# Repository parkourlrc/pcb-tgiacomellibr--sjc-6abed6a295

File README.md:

# Single Joint Control Board (SJC)

- 3 Encoder inputs
- 2 Isolated inputs
- 2 Endstop inputs
- 2 Digital outputs
- Servomotor interface with current sense and pwm output

## Communication library:  

1. Install packages and deps.:
    ```
    sudo apt update
    sudo apt install build-essential git g++ cmake manpages-dev nlohmann-json3-dev
    sudo apt install libmodbus-dev
    ```

2. Acquire SJC packages:
    ``` 
    git clone https://github.com/tgiacomellibr/sjc.git
    ```

3. Create build directory:
    ```
    cd sjc/software
    mkdir -p build && cd build
    ```

4. Configure, compile and install system-wide (default prefix `/usr/local`):
    ```
    cmake ..
    make
    sudo make install
    sudo ldconfig
    ```

    > To install in a custom location instead, pass `-DCMAKE_INSTALL_PREFIX=/path/to/install` to `cmake` (e.g. `$HOME/.local`). In that case `sudo` is not required and you may need to extend `LD_LIBRARY_PATH` / `CMAKE_PREFIX_PATH` to find the library.

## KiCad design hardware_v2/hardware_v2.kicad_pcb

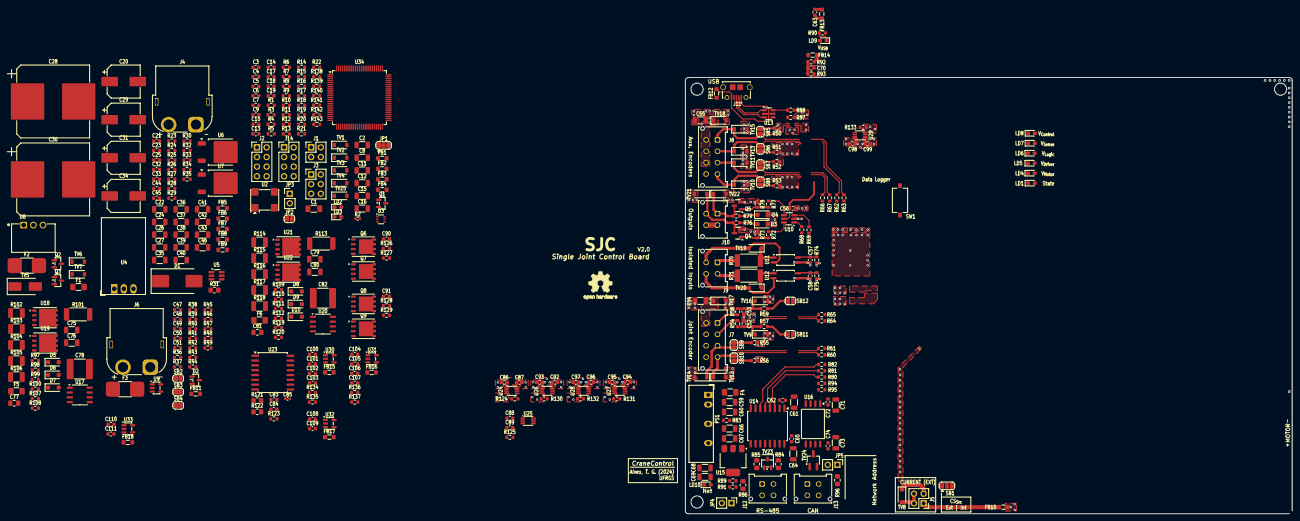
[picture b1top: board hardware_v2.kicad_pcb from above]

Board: 4 copper layers, 160.0 x 115.0 mm, 403 parts (0 on the bottom side), 212 nets.

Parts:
C1: 4.7uF 10% 50V; C_1206_3216Metric_Pad1.33x1.80mm_HandSolder
C2, C8, C11, C12, C38, C39, C54, C55, C67, C68, C76, C80: 1uF 10% 50V; C_1206_3216Metric
C3, C5, C6, C7, C9, C10, C13, C14, C17, C18, C19, C25, C32, C33, C44, C45, C48, C49, C50, C56, C62, C63, C65, C72, C74, C83, C86, C87, C88, C89, C92, C93, C94, C95, C96, C97, C98, C99, C100, C101, C102, C104, C105, C106, C108, C110: 100nF 5% 50V; C_0603_1608Metric
C4, C21, C23, C51, C57, C58, C70, C84, C90, C91, C103, C107, C109, C111: 10nF 5% 50V; C_0603_1608Metric
C15, C16: 2.2uF 10% 50V; C_1206_3216Metric
C20, C34: 47uF 63V 20%; CP_Elec_8x10.5
C22, C24, C26, C27, C35, C36, C40, C41, C42, C46, C60, C61, C64, C66, C69, C71, C73, C75, C79: 10uF 10% 50V; C_1206_3216Metric
C28, C30: 680uF 63V 20%; CP_Elec_18x17.5
C29, C31: 100uF 63V 20%; CP_Elec_8x10.5
C37, C43, C59: 22uF 10% 25V; C_1206_3216Metric
C47: 1.5nF 5% 50V; C_0603_1608Metric
C52, C53: 22nF 5% 50V; C_0603_1608Metric
C77, C81: 100nF 5% 50V; C_0805_2012Metric_Pad1.18x1.45mm_HandSolder
C78, C82: 22uF 20% 50V; C_2220_5750Metric
C85: 220pF 5% 50V; C_0402_1005Metric_Pad0.74x0.62mm_HandSolder
D1: B560C; D_SMC_Handsoldering
D2: BAT54S; SOT-23
D3, D4, D5, D6, D7, D8, D9, D10: PMEG60T30ELR; D_SOD-123F
F1, F5, F6: 30V 1100mA; Fuse_1206_3216Metric_Pad1.42x1.75mm_HandSolder
F2, F3: 40A 63V; Fuse_2410_6125Metric_CB61F
F4: 13.2V 500mA; Fuse_1206_3216Metric_Pad1.42x1.75mm_HandSolder
FB1, FB2, FB3, FB4, FB5, FB6, FB7, FB8, FB9, FB10, FB11, FB12, FB13, FB14, FB15, FB16, FB17, FB18: 220R 3A; L_0805_2012Metric_Pad1.05x1.20mm_HandSolder
H1, H2, H3, H4: MountingHole; MountingHole_3.2mm_M3_ISO7380
J1: Aux Usart; PinHeader_2x02_P2.54mm_Vertical
J2: PROG_{DBG}; PinHeader_2x04_P2.54mm_Vertical
J3: NET ADDRESS; PinHeader_2x03_P2.54mm_Vertical
J4: V_{POWER}; AMASS_XT60PW-F_1x02_P7.20mm_Horizontal
J5: EXT-CS; PinHeader_2x02_P2.54mm_Vertical
J6: Motor; AMASS_XT60PW-F_1x02_P7.20mm_Horizontal
J7: Joint encoders; Molex_Micro-Fit_3.0_43045-0812_2x04_P3.00mm_Vertical
J8: Aux. encoders; Molex_Micro-Fit_3.0_43045-0812_2x04_P3.00mm_Vertical
J9: Isolated Inputs; Molex_Micro-Fit_3.0_43045-0412_2x02_P3.00mm_Vertical
J10: Outputs; Molex_Micro-Fit_3.0_43045-0412_2x02_P3.00mm_Vertical
J11: AMPHENOL_10118194-0001LF
J12, J13: RS-485; Molex_Micro-Fit_3.0_43045-0412_2x02_P3.00mm_Vertical
J14: SPI; PinHeader_2x04_P2.54mm_Vertical
JP1: CS_AD_SEL; SolderJumper-3_P1.3mm_Bridged12_RoundedPad1.0x1.5mm
JP2: CS_AD_SEL; SolderJumper-2_P1.3mm_Open_RoundedPad1.0x1.5mm
JP3: Boot; PinHeader_1x02_P2.54mm_Vertical
JP4, JP5: RS-485 TERM; PinHeader_1x02_P2.54mm_Vertical
LD1, LD2, LD3, LD4, LD5, LD6, LD7, LD8, LD9, LD10: 1.8V @ 5mA; LED_0603_1608Metric_Pad1.05x0.95mm_HandSolder
PS1: IB0512LS-1WR3; IB_LS-1WR3
Q1: BC817; SOT-23
Q2, Q3, Q4, Q5: NDS7002A; SOT-23
Q6, Q7, Q8, Q9: SI7149ADP; PowerPAK_SO-8_Single
R1, R27, R28, R49, R57, R59, R72, R77, R98, R110: 1k 1%; R_0603_1608Metric
R2: 47R 1%; R_0402_1005Metric_Pad0.72x0.64mm_HandSolder
R3, R14, R15, R16, R17, R23, R26, R36, R43, R89, R123: 10k 1%; R_0603_1608Metric
R4, R21, R22, R35: 330R 1%; R_0603_1608Metric
R5, R6, R8, R9, R10, R11, R12, R13, R18, R19, R20, R44, R45, R46, R47, R60, R61, R62, R63, R64, R65, R66, R67, R68, R69, R80, R81, R82, R94, R95, R97, R109, R138, R139, R140, R141, R142, R143: 33R 1%; R_0603_1608Metric
R7, R24, R25, R29, R30, R41, R73, R78, R83, R99, R100, R107, R108, R111, R112, R119, R120, R124, R125, R127, R129, R130, R131, R132, R133: 100k 1%; R_0603_1608Metric
R31: 5.62k 5% 250mW; R_0805_2012Metric_Pad1.20x1.40mm_HandSolder
R32, R33, R74, R75, R76, R79: 2k 5%; R_0603_1608Metric
R34, R90, R91: 680R 1%; R_0603_1608Metric
R37, R38: 1.1k 0.1%; R_0603_1608Metric
R39: 560R 0.1%; R_0603_1608Metric
R40, R42, R48, R134, R135, R136, R137: 1.58k 0.1%; R_0603_1608Metric
R50, R51, R52, R53, R55, R56: 2k7 1%; R_0603_1608Metric
R54, R58: 1.5k 1%; R_0603_1608Metric
R70, R71: 1.6k 5% 1W; R_2512_6332Metric_Pad1.40x3.35mm_HandSolder
R84, R85: 10R 5% 1/2W; R_0805_2012Metric_Pad1.20x1.40mm_HandSolder
R86, R96: 120R 0.1% 1/8W; R_0805_2012Metric_Pad1.20x1.40mm_HandSolder
R87, R88: 22R 1%; R_0603_1608Metric
R92: 33k 0.1%; R_0603_1608Metric
R93, R126, R128: 82k 0.1%; R_0603_1608Metric
R101, R113: 2R 5% 2W; R_2512_6332Metric_Pad1.40x3.35mm_HandSolder
R102, R105, R114, R117: 10R 1% 500mW; R_1210_3225Metric_Pad1.30x2.65mm_HandSolder
R103, R106, R115, R118: 62R 1% 500mW; R_1210_3225Metric_Pad1.30x2.65mm_HandSolder
R104, R116: 0R 1% 500mW; R_1210_3225Metric_Pad1.30x2.65mm_HandSolder
R121: 8k2 1% 1/8W; R_0805_2012Metric_Pad1.20x1.40mm_HandSolder
R122: 1k5 1% 1/8W; R_0805_2012Metric_Pad1.20x1.40mm_HandSolder
SB1: CS_SEL; SolderJumper-3_P1.3mm_Open_RoundedPad1.0x1.5mm
SB2, SB5, SB6, SB7, SB8, SB9, SB10, SB11, SB12: SolderJumper-2_P1.3mm_Open_RoundedPad1.0x1.5mm
SB3, SB4: SolderJumper-2_P1.3mm_Bridged2Bar_RoundedPad1.0x1.5mm
SW1: Tactile Switch; SW_Tactile_SPST_NO_Straight_CK_PTS636Sx25SMTRLFS
SYM1: Logo_Open_Hardware_Small; OSHW-Logo2_9.8x8mm_SilkScreen
TV1, TV2, TV3, TV4, TV7, TV25: PTVS3V3S1UR; D_SOD-123
TV5: SMBJ30A; D_SMB_Handsoldering
TV6, TV8, TV9, TV10, TV11, TV13, TV15, TV16, TV18: PTVS5V0S1UR; D_SOD-123
TV12, TV14, TV17, TV21, TV22: PTVS12VS1UR; D_SOD-123
TV19, TV20: PTVS30VS1UR; D_SOD-123
TV23: SM712; SOT-23-3
TV24: PESD2CANFD24L; SOT-23W_Handsoldering
U2: YSO110TR-16MHz; Oscillator_SMD_YXC_YSO110TR_7050-4Pin_7.0x5.0mm
U3: 74LVC2G17GW; SOT-363_SC-70-6
U4: R-78K12-2.0L; Converter_DCDC_RECOM_R-78K-2.0L_THT
U5, U10: SN74LVC2G04; SOT-23-6_Handsoldering
U6: NCP1117DT50; TO-252-2
U7: NCP1117DT33; TO-252-2
U8: VXO78012-1000; CONV_VXO78012-1000
U9, U30, U31, U32, U33: TLV9051; SOT-23-5
U11, U12: TLP291; SOP-4_4.4x2.6mm_P1.27mm
U13: USBLC6-4SC6; SOT-23-6
U14: ISO1430B; SOIC-16W_7.5x10.3mm_P1.27mm
U15: LD1117S50TR; SOT-223-3_TabPin2
U16: ISO1042; SOIC-8_7.5x5.85mm_P1.27mm
U17, U20: 2ED2184S06F; Infineon_PG-DSO-8-24_4x5mm
U18, U19, U21, U22: IAUC100N04S6N028; Infineon_PG-TDSON-8_6.15x5.15mm
U23: ACS733KLATR-40AB; SOIC-16W_7.5x10.3mm_P1.27mm
U24, U25, U26, U27, U28, U29: 74LVC2T45DC; VSSOP-8_2.3x2mm_P0.5mm
U34: STM32H750VBTx; LQFP-100_14x14mm_P0.5mm

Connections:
+3V3: C1.2, C2.2, C3.2, C5.2, C7.2, C9.2, C10.2, C11.2, C13.2, C19.1, C25.1, C42.2, C45.2, C56.1, C61.2, C62.1, C71.2, C72.1, C86.2, C88.2, C93.1, C95.1, C97.1, C99.1, D2.2, FB1.1, FB3.2, FB11.2, FB15.2, FB16.2, FB17.2, FB18.2, J1.3, J2.2, J3.1, J3.3, J3.5, J14.5, JP3.1, LD1.2 (A), LD8.2 (A), R24.2, R25.2, R74.2, R75.2, R124.2, R125.2, TV1.1 (K), TV2.1 (K), TV7.1 (K), TV25.1 (K), U3.5 (VCC), U5.5 (V_{CC}), U7.2 (VO), U10.5 (V_{CC}), U14.1 (VCC1), U16.1 (VCC1), U24.1 (VCCA), U25.1 (VCCA), U26.1 (VCCA), U27.1 (VCCA), U28.1 (VCCA), U29.1 (VCCA), U34.6 (VBAT), U34.11 (VDD), U34.27 (VDD), U34.50 (VDD), U34.75 (VDD), U34.100 (VDD)
+3V3A: C4.2, C6.2, C8.2, FB1.2, R2.2, U34.21 (VDDA)
+3V3_OSC: C18.1, FB3.1, R17.2, U2.4 (V_{DD})
+3V3_SENSE: C83.1, C84.1, R121.1, R123.2, U23.15 (VCC), U23.16 (VCC)
+5V: C41.2, C44.2, C54.2, C55.2, C87.1, C89.1, C92.2, C94.2, C96.2, C98.2, D3.2 (A), D4.2 (A), F4.2, FB10.1, J7.5, J7.7, J8.5, J8.7, LD7.2 (A), R50.1, R51.1, R52.1, R53.1, R55.2, R56.2, TV6.1 (K), TV17.1 (K), TV18.1 (K), U6.2 (VO), U24.8 (VCCB), U25.8 (VCCB), U26.8 (VCCB), U27.8 (VCCB), U28.8 (VCCB), U29.8 (VCCB)
+5V_ISO: C64.1, C65.1, C68.2, C69.2, C73.1, C74.1, R89.2, R91.1, U14.16 (VCC2), U15.2 (VO), U16.8 (VCC2)
+5V_USB: FB14.2, J11.1 (VBUS), LD9.2 (A), U13.5 (VBUS)
+12V: C32.2, C33.2, C43.2, C46.2, FB6.2, FB8.1, LD6.2 (A), U8.3 (+V_{OUT})
/Communication/485_XCVR_DE: R81.1, U14.4 (~RE), U14.5 (DE)
/Communication/485_XCVR_DI: R82.1, U14.6 (D)
/Communication/485_XCVR_RO: R80.2, U14.3 (R)
/Communication/+12V_ISO_DC: C66.2, C67.2, PS1.6 (+Vout), R83.2, U15.3 (VI)
/Communication/CAN_XCVR_RX: R94.2, U16.3 (RXD)
/Communication/CAN_XCVR_TX: R95.1, U16.2 (TXD)
/Communication/CAN_{H}: J13.2, R96.1, TV24.2 (K2), U16.7 (CANH)
/Communication/CAN_{L}: J13.1, JP5.2, TV24.1 (K1), U16.6 (CANL)
/Communication/COM_USB_V_{BUS}_SIG: C70.2, R92.2, R93.2
/Communication/RS_485_{A}: J12.1, R85.1, R86.1, TV23.1
/Communication/RS_485_{B}: J12.2, JP4.1, R84.1, TV23.2
/Communication/RS_{A}: R85.2, U14.12 (A)
/Communication/RS_{B}: R84.2, U14.13 (B)
/Communication/USB_D+: J11.3 (D+), R87.2, U13.3 (I/O2), U13.4 (I/O3)
/Communication/USB_D-: J11.2 (D-), R88.2, U13.1 (I/O1), U13.6 (I/O4)
/Control/BOOT: JP3.2, R7.2
/Control/CURRENT_SIGNAL_FILT: JP1.2 (C), R40.2, SB4.2 (B)
/Control/DBG_USART_TX: J2.5, R12.2
/Control/GP_ISO_IN_A: C57.2, R74.1, U11.4
/Control/GP_ISO_IN_B: C58.2, R75.1, U12.4
/Control/JTCK/SWCLK: J2.7, R11.2
/Control/JTDI: J2.6, R9.2
/Control/JTDO/TRACESWO: J2.4, R8.2
/Control/JTMS/SWDIO: J2.8, R10.2
/Control/MOTOR_INPUT_VOLTAGE_SIG: R49.2, U33.1, U33.4 (-)
/Control/MotorDriver_{EN}: C21.2, R24.1, U5.1 (1A)
/Control/MotorPSU_{EN}: C23.2, R25.1, U5.3 (2A)
/Control/NET_ADDR_A: J3.2, R14.1
/Control/NET_ADDR_B: J3.4, R15.1
/Control/NET_ADDR_C: J3.6, R16.1
/Control/NJTRST: J2.3, R13.2
/Control/NRST: C17.2, SW1.2
/Control/R_MOT_HI_{PWM}: JP2.1 (A), R46.2
/Control/SPI_CSEL_{PIN}: J14.6, R142.1
/Control/SPI_INT_{PIN}: J14.8, R143.1
/Control/SPI_MISO_{PIN}: J14.2, R140.1
/Control/SPI_MOSI_{PIN}: J14.1, R139.1
/Control/SPI_RST_{PIN}: J14.4, R141.1
/Control/SPI_SCK_{PIN}: J14.7, R138.1
/Control/X_{OSC}: R18.2, U2.3 (OUT)
/Encoders/Aux encoder A level shifter/OUT_{A}: R62.2, U28.2 (1A)
/Encoders/Aux encoder A level shifter/OUT_{B}: R63.2, U28.3 (2A)
/Encoders/Aux encoder B level shifter/OUT_{A}: R66.2, U29.2 (1A)
/Encoders/Aux encoder B level shifter/OUT_{B}: R67.2, U29.3 (2A)
/Encoders/JNT_ENC_A: J7.3, SB9.1 (A), TV14.1 (K), U26.6 (2B)
/Encoders/JNT_ENC_B: J7.4, SB10.1 (A), TV12.1 (K), U26.7 (1B)
/Encoders/JNT_ESTOP_A: J7.2, R54.1
/Encoders/JNT_ESTOP_B: J7.1, R58.1
/Encoders/JNT_SW_A: C52.2, R54.2, R57.1, TV9.1 (K), U27.7 (1B)
/Encoders/JNT_SW_B: C53.2, R58.2, R59.1, TV16.1 (K), U27.6 (2B)
/Encoders/Joint encoder level shifter/OUT_{A}: R60.2, U26.2 (1A)
/Encoders/Joint encoder level shifter/OUT_{B}: R61.2, U26.3 (2A)
/Encoders/Joint switch level shifter/OUT_{A}: R64.2, U27.2 (1A)
/Encoders/Joint switch level shifter/OUT_{B}: R65.2, U27.3 (2A)
/Encoders/S1_ENC_A: J8.4, SB8.1 (A), TV10.1 (K), U29.7 (1B)
/Encoders/S1_ENC_B: J8.3, SB7.1 (A), TV11.1 (K), U29.6 (2B)
/Encoders/S2_ENC_A: J8.2, SB6.1 (A), TV13.1 (K), U28.7 (1B)
/Encoders/S2_ENC_B: J8.1, SB5.1 (A), TV15.1 (K), U28.6 (2B)
/GPIOs/ISO_IN_A: J9.1, R70.2
/GPIOs/ISO_IN_A_{COM}: J9.3, TV19.2 (A), U11.2
/GPIOs/ISO_IN_B: J9.2, R71.2
/GPIOs/ISO_IN_B_{COM}: J9.4, TV20.2 (A), U12.2
/GPIOs/OUT_A: J10.3, Q4.3 (D), R76.1, TV21.1 (K)
/GPIOs/OUT_B: J10.1, Q5.3 (D), R79.1, TV22.1 (K)
/Motor/CS_ACS733: C85.1, SB1.3 (B), U23.12 (VIOUT)
/Motor/CS_EXT: R38.2, R39.1, SB1.1 (A)
/Motor/CS_MEAS_FILT_IN: R134.1, SB3.2 (B)
/Motor/FLT_ACS733: R123.1, U23.13 (~FAULT)
/Motor/INNER+: F3.1, U23.1 (IP+), U23.2 (IP+), U23.3 (IP+), U23.4 (IP+)
/Motor/INNER-: R116.1, R119.1, U21.1 (S), U21.2 (S), U21.3 (S), U22.5 (D), U23.5 (IP-), U23.6 (IP-), U23.7 (IP-), U23.8 (IP-)
/Motor/Input buffer1/In: C47.2, R41.1, R43.2, U33.3 (+)
/Motor/Input buffer/In: R36.2, U32.3 (+)
/Motor/Input buffer/Out: SB3.1 (A), U32.1, U32.4 (-)
/Motor/LP-Filter First stage/Out: C100.1, R136.1, U30.1, U30.4 (-)
/Motor/LP-Filter Second stage/Out: C104.1, SB4.1 (A), U31.1, U31.4 (-)
/Motor/L_EN: R110.2, U24.6 (2B)
/Motor/L_PWM: R109.2, U24.7 (1B)
/Motor/Left half-bridge/BST_VCC: C79.1, C80.1, D8.2 (A), F6.2, U20.5 (VCC)
/Motor/Left half-bridge/HO: D9.1 (K), R115.2, U20.7 (HO)
/Motor/Left half-bridge/HSG: R114.2, R115.1, R119.2, U21.4 (G)
/Motor/Left half-bridge/H_{MID}: D9.2 (A), R114.1
/Motor/Left half-bridge/LO: D10.1 (K), R118.2, U20.4 (LO)
/Motor/Left half-bridge/LSG: R117.2, R118.1, R120.2, U22.4 (G)
/Motor/Left half-bridge/L_{MID}: D10.2 (A), R117.1
/Motor/Left half-bridge/PWM_PD: R109.1, R111.2, U20.1 (IN)
/Motor/Left half-bridge/SD_PD: R110.1, R112.2, U20.2 (~SD)
/Motor/Left half-bridge/VS: C81.1, R116.2, U20.6 (VS)
/Motor/Left motor level shifter/IN_{A}: R44.1, U24.2 (1A)
/Motor/Left motor level shifter/IN_{B}: R45.1, U24.3 (2A)
/Motor/M+: F3.2, J6.1
/Motor/M-: J6.2, R104.1, R107.1, U18.1 (S), U18.2 (S), U18.3 (S), U19.5 (D)
/Motor/R_EN: R98.2, U25.6 (2B)
/Motor/R_PWM: R97.2, U25.7 (1B)
/Motor/Right half-bridge/BST_VCC: C75.1, C76.1, D5.2 (A), F5.2, U17.5 (VCC)
/Motor/Right half-bridge/HO: D6.1 (K), R103.2, U17.7 (HO)
/Motor/Right half-bridge/HSG: R102.2, R103.1, R107.2, U18.4 (G)
/Motor/Right half-bridge/H_{MID}: D6.2 (A), R102.1
/Motor/Right half-bridge/LO: D7.1 (K), R106.2, U17.4 (LO)
/Motor/Right half-bridge/LSG: R105.2, R106.1, R108.2, U19.4 (G)
/Motor/Right half-bridge/L_{MID}: D7.2 (A), R105.1
/Motor/Right half-bridge/PWM_PD: R97.1, R99.2, U17.1 (IN)
/Motor/Right half-bridge/SD_PD: R98.1, R100.2, U17.2 (~SD)
/Motor/Right half-bridge/VS: C77.1, R104.2, U17.6 (VS)
/Motor/Right motor level shifter/IN_{A}: R46.1, U25.2 (1A)
/Motor/Right motor level shifter/IN_{B}: R47.1, U25.3 (2A)
/Power Supply/DRIVER_~EN_{SIG}: Q2.3 (D), R128.1
/Power Supply/MOTOR_~EN_{SIG}: Q3.3 (D), R126.1
DRIVER_IN_{FUSE}: C20.1, C22.2, C24.2, F1.1, R23.2, U4.1 (+V_{in})
DRIVER_VCC: C29.1, C31.1, F5.1, F6.1, FB5.1, LD5.2 (A)
GND: C1.1, C2.1, C3.1, C5.1, C7.1, C9.1, C10.1, C11.1, C13.1, C15.1, C16.1, C17.1, C19.2, C21.1, C23.1, C25.2, C35.1, C36.1, C38.1, C39.1, C41.1, C42.1, C44.1, C45.1, C47.1, C49.1, C50.2, C51.2, C52.1, C53.1, C54.1, C55.1, C56.2, C57.1, C58.1, C59.1, C60.1, C61.1, C62.2, C70.1, C71.1, C72.2, C86.1, C87.2, C88.1, C89.2, C92.1, C93.2, C94.1, C95.2, C96.1, C97.2, C98.1, C99.2, C101.1, C102.2, C103.2, C105.1, C106.2, C107.2, C108.2, C109.2, C110.2, C111.2, D2.1, FB2.1, FB4.2, FB7.1, FB9.1, FB12.1, J1.1, J2.1, J5.2, J5.4, J7.6, J7.8, J8.6, J8.8, J10.2, J10.4, J14.3, LD2.1 (K), LD3.1 (K), PS1.2 (-Vin), Q1.2 (E), Q4.2 (S), Q5.2 (S), R7.1, R14.2, R15.2, R16.2, R34.2, R35.2, R38.1, R40.1, R43.1, R49.1, R73.1, R78.1, R93.1, R130.1, R131.1, R132.1, R133.1, SB2.2 (B), SB11.2 (B), SB12.2 (B), SW1.1, TV1.2 (A), TV2.2 (A), TV3.2 (A), TV4.2 (A), TV6.2 (A), TV7.2 (A), TV8.2 (A), TV9.2 (A), TV10.2 (A), TV11.2 (A), TV12.2 (A), TV13.2 (A), TV14.2 (A), TV15.2 (A), TV16.2 (A), TV17.2 (A), TV18.2 (A), TV21.2 (A), TV22.2 (A), TV25.2 (A), U3.2 (GND), U5.2 (GND), U6.1 (GND), U7.1 (GND), U9.2 (V-), U10.2 (GND), U11.3, U12.3, U14.2 (GND1), U14.8 (GND1), U16.4 (GND1), U24.4 (GND), U25.4 (GND), U26.4 (GND), U27.4 (GND), U28.4 (GND), U29.4 (GND), U30.2 (V-), U31.2 (V-), U32.2 (V-), U33.2 (V-), U34.10 (VSS), U34.26 (VSS), U34.49 (VSS), U34.74 (VSS), U34.99 (VSS)
GNDA: C4.1, C6.1, C8.1, C12.1, C14.1, FB2.2, U34.19 (VSSA)
GND_ISO: C64.2, C65.2, C66.1, C67.1, C68.1, C69.1, C73.2, C74.2, J12.3, J12.4, J13.3, J13.4, LD10.1 (K), PS1.4 (-Vout), R83.1, R89.1, TV23.3, TV24.3 (CC), U14.9 (GND2), U14.15 (GND2), U15.1 (GND), U16.5 (GND2)
GND_OSC: C18.2, FB4.1, U2.2 (GND)
GND_SENSE: C83.2, C84.2, C85.2, R122.2, U23.9 (GND), U23.10 (GND), U23.11 (PROGRAM)
GND_USB: C63.1, FB12.2, FB13.2, J11.5 (GND), R90.2, U13.2 (GND)
unnamed: C48.2, R42.2, R48.1
unnamed: C63.2, FB13.1, J11.S1 (Shield), J11.S2 (Shield), J11.S3 (Shield), J11.S4 (Shield), J11.S5 (Shield), J11.S6 (Shield)
unnamed: C90.2, Q6.1 (S), Q6.2 (S), Q6.3 (S), Q7.1 (S), Q7.2 (S), Q7.3 (S), R127.2
unnamed: C91.2, Q8.1 (S), Q8.2 (S), Q8.3 (S), Q9.1 (S), Q9.2 (S), Q9.3 (S), R129.2
unnamed: C100.2, R134.2, R135.1
unnamed: C104.2, R136.2, R137.1
unnamed: D3.1 (K), R76.2
unnamed: D4.1 (K), R79.2
unnamed: D5.1 (K), R101.2
unnamed: D8.1 (K), R113.2
unnamed: FB14.1, R92.1
unnamed: J1.2, R6.2, TV3.1 (K)
unnamed: J1.4, R5.2, TV4.1 (K)
unnamed: FB10.2, J5.1
unnamed: J5.3, R39.2, TV8.1 (K)
unnamed: JP2.2 (B), R1.2
unnamed: JP4.2, R86.2
unnamed: JP5.1, R96.2
unnamed: LD1.1 (K), R4.1
unnamed: LD2.2 (A), R21.1
unnamed: LD3.2 (A), R22.1
unnamed: LD4.1 (K), R31.1
unnamed: LD5.1 (K), R32.1
unnamed: LD6.1 (K), R33.1
unnamed: LD7.1 (K), R34.1
unnamed: LD8.1 (K), R35.1
unnamed: LD9.1 (K), R90.1
unnamed: LD10.2 (A), R91.2
unnamed: C59.2, C60.2, F4.1, PS1.1 (+Vin)
unnamed: Q1.1 (B), R3.2
unnamed: Q1.3 (C), R4.2
unnamed: Q2.1 (G), R27.1, R29.2
unnamed: Q3.1 (G), R28.1, R30.2
unnamed: Q4.1 (G), R72.1, R73.2
unnamed: Q5.1 (G), R77.1, R78.2
unnamed: C90.1, Q6.4 (G), Q7.4 (G), R126.2, R127.1
unnamed: C91.1, Q8.4 (G), Q9.4 (G), R128.2, R129.1
unnamed: D2.3, R36.1, R37.1, SB1.2 (C)
unnamed: R37.2, SB2.1 (A)
unnamed: R50.2, SB5.2 (B)
unnamed: R51.2, SB6.2 (B)
unnamed: R52.2, SB7.2 (B)
unnamed: R53.2, SB8.2 (B)
unnamed: R55.1, SB9.2 (B)
unnamed: R56.1, SB10.2 (B)
unnamed: R57.2, SB11.1 (A)
unnamed: R59.2, SB12.1 (A)
unnamed: R70.1, TV19.1 (K), U11.1
unnamed: R71.1, TV20.1 (K), U12.1
unnamed: R17.1, U2.1 (En)
unnamed: R19.1, U3.1 (1A)
unnamed: R21.2, U3.6 (1Y)
unnamed: R20.1, U3.3 (2A)
unnamed: R22.2, U3.4 (2Y)
unnamed: C26.2, C27.2, FB5.2, R26.2, U4.3 (+V_{out})
unnamed: R27.2, U5.6 (1Y)
unnamed: R28.2, U5.4 (2Y)
unnamed: C35.2, C38.2, FB6.1, U6.3 (VI)
unnamed: C36.2, C39.2, FB8.2, U7.3 (VI)
unnamed: C49.2, R48.2, U9.3 (+)
unnamed: C48.1, U9.1, U9.4 (-)
unnamed: C50.1, C51.1, FB11.1, U9.5 (V+)
unnamed: R68.1, U10.1 (1A)
unnamed: R72.2, U10.6 (1Y)
unnamed: R69.1, U10.3 (2A)
unnamed: R77.2, U10.4 (2Y)
unnamed: C77.2, R101.1, U17.8 (VB)
unnamed: C81.2, R113.1, U20.8 (VB)
unnamed: R121.2, R122.1, U23.14 (VOC)
unnamed: R124.1, U24.5 (DIR)
unnamed: R125.1, U25.5 (DIR)
unnamed: R130.2, U26.5 (DIR)
unnamed: R131.2, U27.5 (DIR)
unnamed: R132.2, U28.5 (DIR)
unnamed: R133.2, U29.5 (DIR)
unnamed: C101.2, R135.2, U30.3 (+)
unnamed: C102.1, C103.1, FB15.1, U30.5 (V+)
unnamed: C105.2, R137.2, U31.3 (+)
unnamed: C106.1, C107.1, FB16.1, U31.5 (V+)
unnamed: C108.1, C109.1, FB17.1, U32.5 (V+)
unnamed: C110.1, C111.1, FB18.1, U33.5 (V+)
PGND: C20.2, C22.1, C24.1, C26.1, C27.1, C28.2, C29.2, C30.2, C31.2, C32.1, C33.1, C34.2, C37.1, C40.1, C43.1, C46.1, C75.2, C76.2, C78.2, C79.2, C80.2, C82.2, FB7.2, FB9.2, J4.1, Q2.2 (S), Q3.2 (S), R23.1, R26.1, R29.1, R30.1, R31.2, R32.2, R33.2, R99.1, R100.1, R108.1, R111.1, R112.1, R120.1, TV5.2 (A), U4.2 (Gnd), U8.2 (GND), U17.3 (COM), U19.1 (S), U19.2 (S), U19.3 (S), U20.3 (COM), U22.1 (S), U22.2 (S), U22.3 (S)
V_{BPS}+: F1.2, Q9.5 (D)
V_{MOTOR}: C78.1, C82.1, U18.5 (D), U21.5 (D)
V_{PWR}+: F2.1, J4.2
V_{PWR}_Fuse+: D1.2 (A), F2.2, Q6.5 (D), Q8.5 (D), TV5.1 (K)
V_{PWR}_Rect+: C34.1, C37.2, C40.2, D1.1 (K), U8.1 (+V_{IN})
V_{PWR}_Src+: C28.1, C30.1, LD4.2 (A), Q7.5 (D), R41.2
V_{REF}+: C12.2, C14.2, R2.1
